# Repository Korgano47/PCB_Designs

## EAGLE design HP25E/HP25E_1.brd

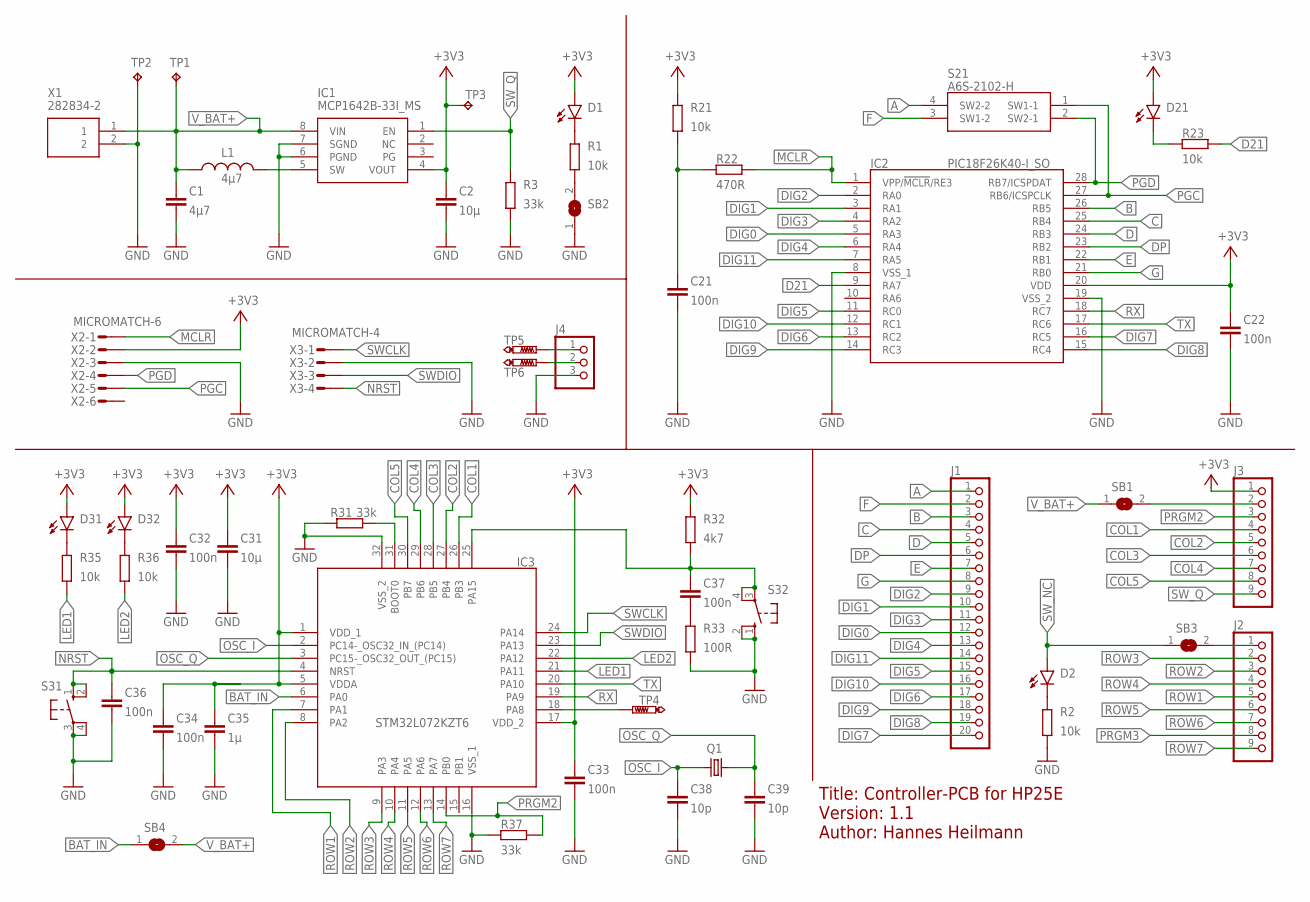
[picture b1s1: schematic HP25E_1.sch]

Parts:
C1: 4µ7; C1206K
C2, C31: 10µ; C1206K
C21, C22, C32, C33, C34, C36, C37: 100n; C0805K
C35: 1µ; C1206K
C38, C39: 10p; C0805K
D1, D2, D21, D31, D32: LEDSML0805; SML0805
IC1: MCP1642B-33I_MS; SOP65P490X110-8N
IC2: PIC18F26K40-I_SO; SOIC127P1030X265-28N
IC3: STM32L072KZT6; QFP80P900X900X160-32N
J1: PINHD-1X20-BIG; 1X20-BIG
J2, J3: PINHD-1X9; 1X09-BIG
J4: PINHD-1X3; 1X03
L1: 4µ7; L4532P
Q1: CRYSTALMM20SS; MM20SS
R1, R2, R21, R23, R35, R36: 10k; R0805
R3, R31, R37: 33k; R0805
R22: 470R; R0805
R32: 4k7; R0805
R33: 100R; R0805
S21: A6S-2102-H; SOP254P980X450-4N
S31, S32: 10-XX; B3F-10XX
SB1, SB2, SB3, SB4: SJ
TP1, TP2, TP3: TPB1,27; B1,27
TP4: PTR1B1,27; B1,27
TP5, TP6: PTR1PAD1-13; P1-13
X1: 282834-2; SHDR2W85P0X254_1X2_554X650X103
X2: MICROMATCH-6
X3: MICROMATCH-4

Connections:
+3V3: C2.1, C22.1, C31.1, C32.1, C33.1, C34.1, C35.1, D1.A, D21.A, D31.A, D32.A, IC1.4 (VOUT), IC2.20 (VDD), IC3.1 (VDD_1), IC3.5 (VDDA), IC3.17 (VDD_2), J3.1, R21.2, R32.2, TP3.TP, X2.2
A: J1.1, S21.4 (SW2-2)
B: IC2.26 (RB5), J1.3
BAT_IN: IC3.6 (PA0), SB4.1
C: IC2.25 (RB4), J1.4
COL1: IC3.26 (PB3), J3.4
COL2: IC3.27 (PB4), J3.5
COL3: IC3.28 (PB5), J3.6
COL4: IC3.29 (PB6), J3.7
COL5: IC3.30 (PB7), J3.8
D: IC2.24 (RB3), J1.5
D21: IC2.9 (RA7), R23.1
DIG0: IC2.5 (RA3), J1.12
DIG1: IC2.3 (RA1), J1.10
DIG2: IC2.2 (RA0), J1.9
DIG3: IC2.4 (RA2), J1.11
DIG4: IC2.6 (RA4), J1.13
DIG5: IC2.11 (RC0), J1.15
DIG6: IC2.13 (RC2), J1.17
DIG7: IC2.16 (RC5), J1.20
DIG8: IC2.15 (RC4), J1.19
DIG9: IC2.14 (RC3), J1.18
DIG10: IC2.12 (RC1), J1.16
DIG11: IC2.7 (RA5), J1.14
DP: IC2.23 (RB2), J1.6
E: IC2.22 (RB1), J1.7
F: J1.2, S21.3 (SW1-2)
G: IC2.21 (RB0), J1.8
GND: C1.2, C2.2, C21.2, C22.2, C31.2, C32.2, C33.2, C34.2, C35.2, C36.2, C38.2, C39.2, IC1.6 (PGND), IC1.7 (SGND), IC2.8 (VSS_1), IC2.19 (VSS_2), IC3.16 (VSS_1), IC3.32 (VSS_2), J4.3, R2.1, R3.1, R31.2, R33.1, R37.2, S31.3, S31.4 (P1), S32.1 (S), S32.2 (S1), SB2.1, TP2.TP, X1.2, X2.3, X3.2
LED1: IC3.21 (PA11), R35.1
LED2: IC3.22 (PA12), R36.1
MCLR: IC2.1 (VPP/!MCLR!/RE3), R22.2, X2.1
unnamed: IC1.5 (SW), L1.1
unnamed: D21.C, R23.2
unnamed: C21.1, R21.1, R22.1
unnamed: D1.C, R1.2
unnamed: D2.C, R2.2
unnamed: C37.1, IC3.25 (PA15), R32.1, S32.3, S32.4 (P1)
unnamed: C37.2, R33.2
unnamed: J2.1, SB3.2
unnamed: IC3.31 (BOOT0), R31.1
unnamed: R1.1, SB2.2
unnamed: D32.C, R36.2
unnamed: D31.C, R35.2
unnamed: J4.2, TP6.TP
unnamed: J4.1, TP5.TP
unnamed: IC3.18 (PA8), TP4.TP
NRST: C36.1, IC3.4 (NRST), S31.1 (S), S31.2 (S1), X3.4
OSC_I: C38.1, IC3.2 (PC14-_OSC32_IN_(PC14)), Q1.1
OSC_Q: C39.1, IC3.3 (PC15-_OSC32_OUT_(PC15)), Q1.4 (2)
PGC: IC2.27 (RB6/ICSPCLK), S21.1 (SW1-1), X2.5
PGD: IC2.28 (RB7/ICSPDAT), S21.2 (SW2-1), X2.4
PRGM2: IC3.14 (PB0), J3.3, R37.1
PRGM3: J2.8
ROW1: IC3.7 (PA1), J2.5
ROW2: IC3.8 (PA2), J2.3
ROW3: IC3.9 (PA3), J2.2
ROW4: IC3.10 (PA4), J2.4
ROW5: IC3.11 (PA5), J2.6
ROW6: IC3.12 (PA6), J2.7
ROW7: IC3.13 (PA7), J2.9
RX: IC2.18 (RC7), IC3.19 (PA9)
SWCLK: IC3.24 (PA14), X3.1
SWDIO: IC3.23 (PA13), X3.3
SW_I: J3.2, SB1.2
SW_NC: D2.A, SB3.1
SW_Q: IC1.1 (EN), J3.9, R3.2
TX: IC2.17 (RC6), IC3.20 (PA10)
V_BAT+: C1.1, IC1.8 (VIN), L1.2, SB1.1, SB4.2, TP1.TP, X1.1

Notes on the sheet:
Title: Controller-PCB for HP25E Version: 1.1 Author: Hannes Heilmann

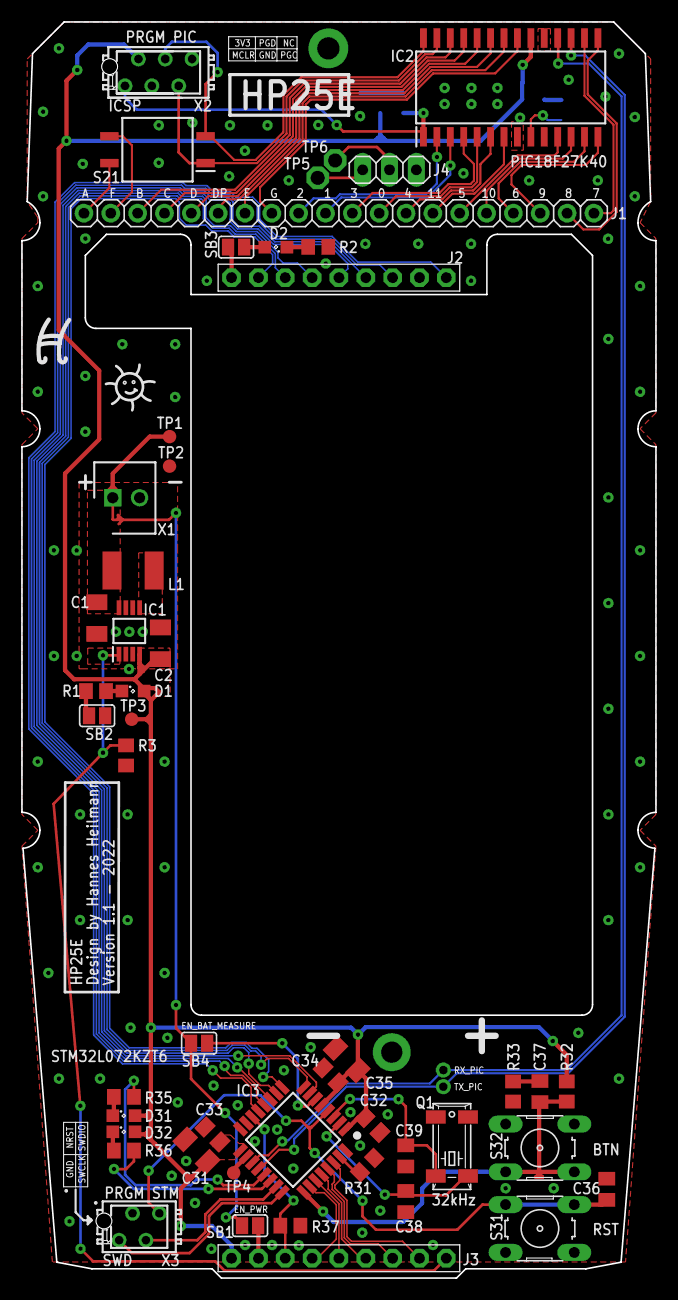
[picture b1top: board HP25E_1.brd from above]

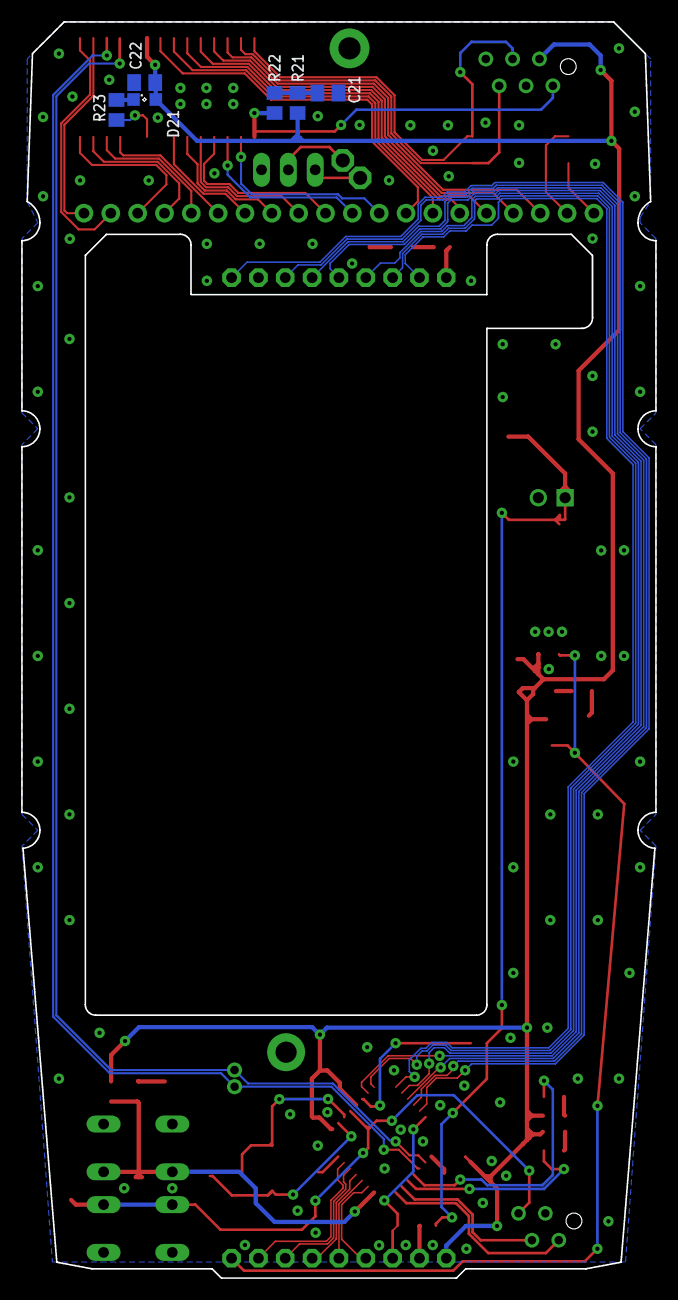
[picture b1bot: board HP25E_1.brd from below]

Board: 2 copper layers, 60.0 x 118.9 mm, 55 parts (6 on the bottom side), 68 nets.

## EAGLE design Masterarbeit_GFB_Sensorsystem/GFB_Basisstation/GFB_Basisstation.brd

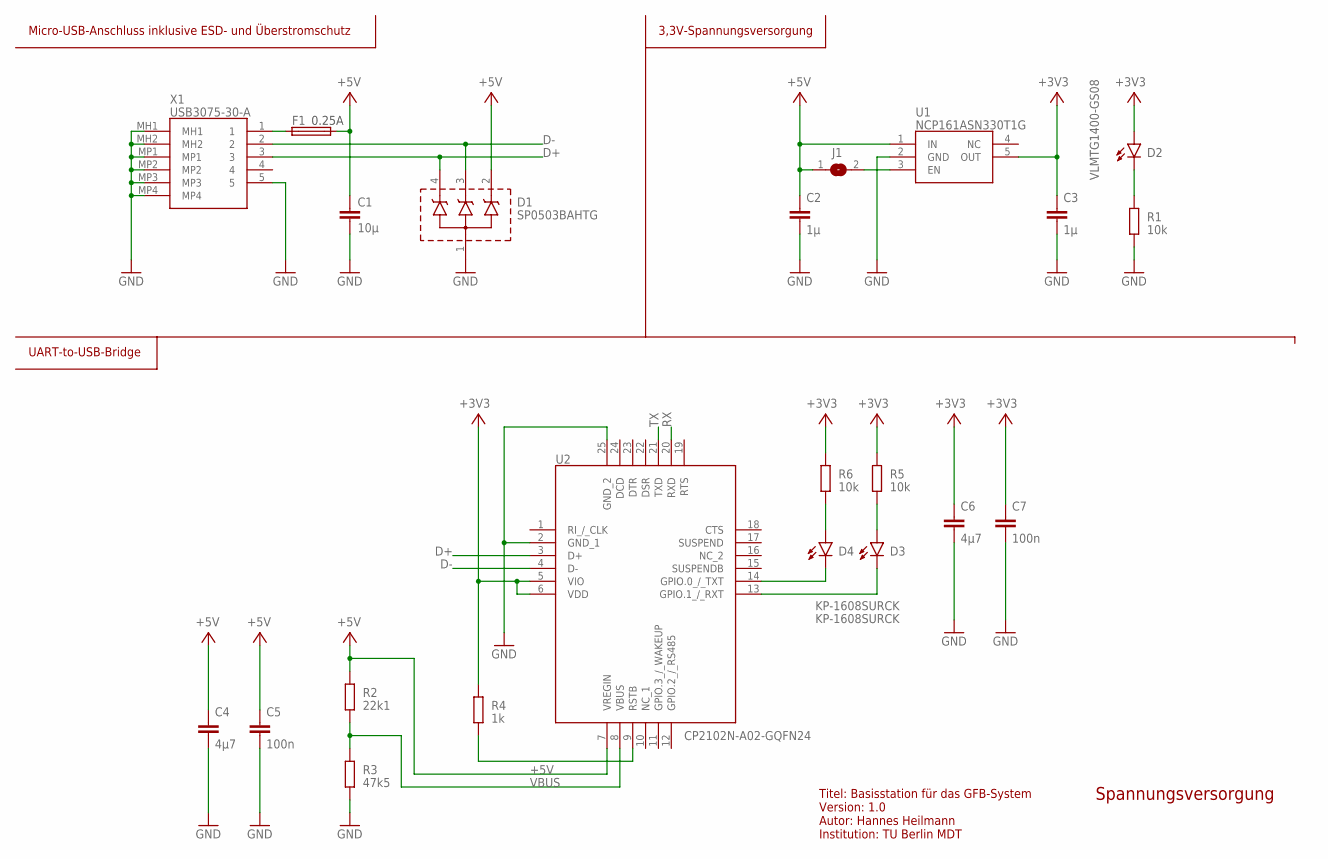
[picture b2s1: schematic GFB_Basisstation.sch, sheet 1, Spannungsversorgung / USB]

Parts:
C1: 10µ; PATCHPOLYGRAPHV1_1608M
C2, C3: 1µ; PATCHPOLYGRAPHV1_1608M
C4, C6: 4µ7; PATCHPOLYGRAPHV1_1608M
C5, C7: 100n; PATCHPOLYGRAPHV1_1608M
D1: SP0503BAHTG
D2: VLMTG1400-GS08; CHIPLED_0603
D3, D4: KP-1608SURCK; CHIPLED_0603
F1: SF-0603FP025F-2; R0603
J1: SJ
R1, R5, R6: 10k; PATCHPOLYGRAPHV1_1608M
R2: 22k1; PATCHPOLYGRAPHV1_1608M
R3: 47k5; PATCHPOLYGRAPHV1_1608M
R4: 1k; PATCHPOLYGRAPHV1_1608M
U1: NCP161ASN330T1G; SOT95P280X145-5N
U2: CP2102N-A02-GQFN24; QFN50P400X400X80-25N
X1: USB3075-30-A; USB307530A

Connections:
+3V3: C3.1, C6.1, C7.1, D2.A, R4.1, R5.1, R6.1, U1.5 (OUT), U2.5 (VIO), U2.6 (VDD); also elsewhere on the board
+5V: C1.1, C2.1, C4.1, C5.1, D1.2 (K_1), F1.2, J1.1, R2.1, U1.1 (IN), U2.7 (VREGIN)
D+: D1.4 (K_3), U2.3 (D+), X1.3
D-: D1.3 (K_2), U2.4 (D-), X1.2
GND: C1.2, C2.2, C3.2, C4.2, C5.2, C6.2, C7.2, D1.1 (COMMON_A), R1.2, R3.2, U1.2 (GND), U2.2 (GND_1), U2.25 (GND_2), X1.5, X1.MH1, X1.MH2, X1.MP1, X1.MP2, X1.MP3, X1.MP4; also elsewhere on the board
unnamed: D2.C, R1.1
unnamed: D3.A, R5.2
unnamed: R4.2, U2.9 (RSTB)
unnamed: D4.A, R6.2
unnamed: F1.1, X1.1
unnamed: D3.C, U2.13 (GPIO.1_/_RXT)
unnamed: D4.C, U2.14 (GPIO.0_/_TXT)
unnamed: J1.2, U1.3 (EN)
RX: U2.20 (RXD); also elsewhere on the board
TX: U2.21 (TXD); also elsewhere on the board
VBUS: R2.2, R3.1, U2.8 (VBUS)

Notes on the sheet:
0.25A
Spannungsversorgung
Titel: Basisstation für das GFB-System Version: 1.0 Autor: Hannes Heilmann Institution: TU Berlin MDT
Micro-USB-Anschluss inklusive ESD- und Überstromschutz
3,3V-Spannungsversorgung
UART-to-USB-Bridge

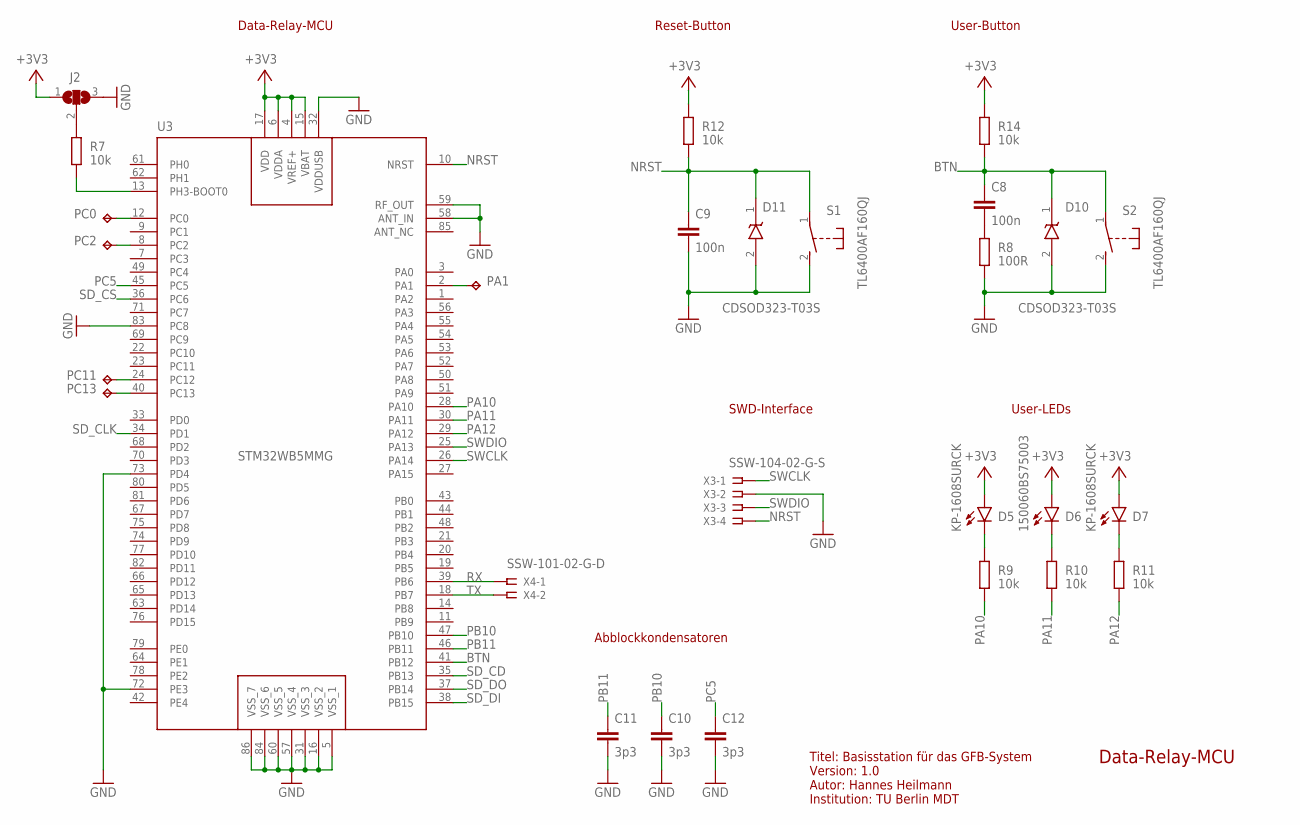
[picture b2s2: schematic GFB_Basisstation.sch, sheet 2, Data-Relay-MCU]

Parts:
C8, C9: 100n; PATCHPOLYGRAPHV1_1608M
C10, C11, C12: 3p3; PATCHPOLYGRAPHV1_1608M
D5, D7: KP-1608SURCK; CHIPLED_0603
D6: 150060BS75003; CHIPLED_0603
D10, D11: CDSOD323-T03S; SOD2513X114N
J2: JUMPER_3JUMPER_3_0603; JUMPER_3_0603
PA1: TPTP06R; TP06R
PC0, PC2, PC11, PC13: TPTP06R; TP06R
R7, R9, R10, R11, R12, R14: 10k; PATCHPOLYGRAPHV1_1608M
R8: 100R; PATCHPOLYGRAPHV1_1608M
S1, S2: TL6400AF160QJ
U3: STM32WB5MMG
X3: SSW-104-02-G-S
X4: SSW-101-02-G-D

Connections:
+3V3: D5.A, D6.A, D7.A, J2.1, R12.1, R14.1, U3.4 (VREF+), U3.6 (VDDA), U3.15 (VBAT), U3.17 (VDD); also elsewhere on the board
BTN: C8.1, D10.1 (K), R14.2, S2.1, U3.41 (PB12)
GND: C9.2, C10.2, C11.2, C12.2, D10.2 (A), D11.2 (A), J2.3, R8.2, S1.2 (S), S2.2 (S), U3.5 (VSS_1), U3.16 (VSS_2), U3.31 (VSS_3), U3.32 (VDDUSB), U3.57 (VSS_4), U3.58 (ANT_IN), U3.59 (RF_OUT), U3.60 (VSS_5), U3.72 (PE3), U3.73 (PD4), U3.83 (PC8), U3.84 (VSS_6), U3.86 (VSS_7), X3.2; also elsewhere on the board
unnamed: PC2.TP, U3.8 (PC2)
unnamed: R7.2, U3.13 (PH3-BOOT0)
unnamed: PC11.TP, U3.24 (PC12)
unnamed: C8.2, R8.1
unnamed: D6.C, R10.1
unnamed: D7.C, R11.1
unnamed: D5.C, R9.1
unnamed: PC13.TP, U3.40 (PC13)
unnamed: J2.2, R7.1
unnamed: PA1.TP, U3.2 (PA1)
NRST: C9.1, D11.1 (K), R12.2, S1.1, U3.10 (NRST), X3.4
PA10: R9.2, U3.28 (PA10)
PA11: R10.2, U3.30 (PA11)
PA12: R11.2, U3.29 (PA12)
PB10: C10.1, U3.47 (PB10)
PB11: C11.1, U3.46 (PB11)
PC0: PC0.TP, U3.12 (PC0)
PC5: C12.1, U3.45 (PC5)
RX: U3.39 (PB6), X4.1; also elsewhere on the board
SD_CD: U3.35 (PB13); also elsewhere on the board
SD_CLK: U3.34 (PD1); also elsewhere on the board
SD_CS: U3.36 (PC6); also elsewhere on the board
SD_DI: U3.38 (PB15); also elsewhere on the board
SD_DO: U3.37 (PB14); also elsewhere on the board
SWCLK: U3.26 (PA14), X3.1
SWDIO: U3.25 (PA13), X3.3
TX: U3.18 (PB7), X4.2; also elsewhere on the board

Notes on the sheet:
STM32WB5MMG
Titel: Basisstation für das GFB-System Version: 1.0 Autor: Hannes Heilmann Institution: TU Berlin MDT
Data-Relay-MCU
Reset-Button
User-Button
SWD-Interface
User-LEDs
Abblockkondensatoren

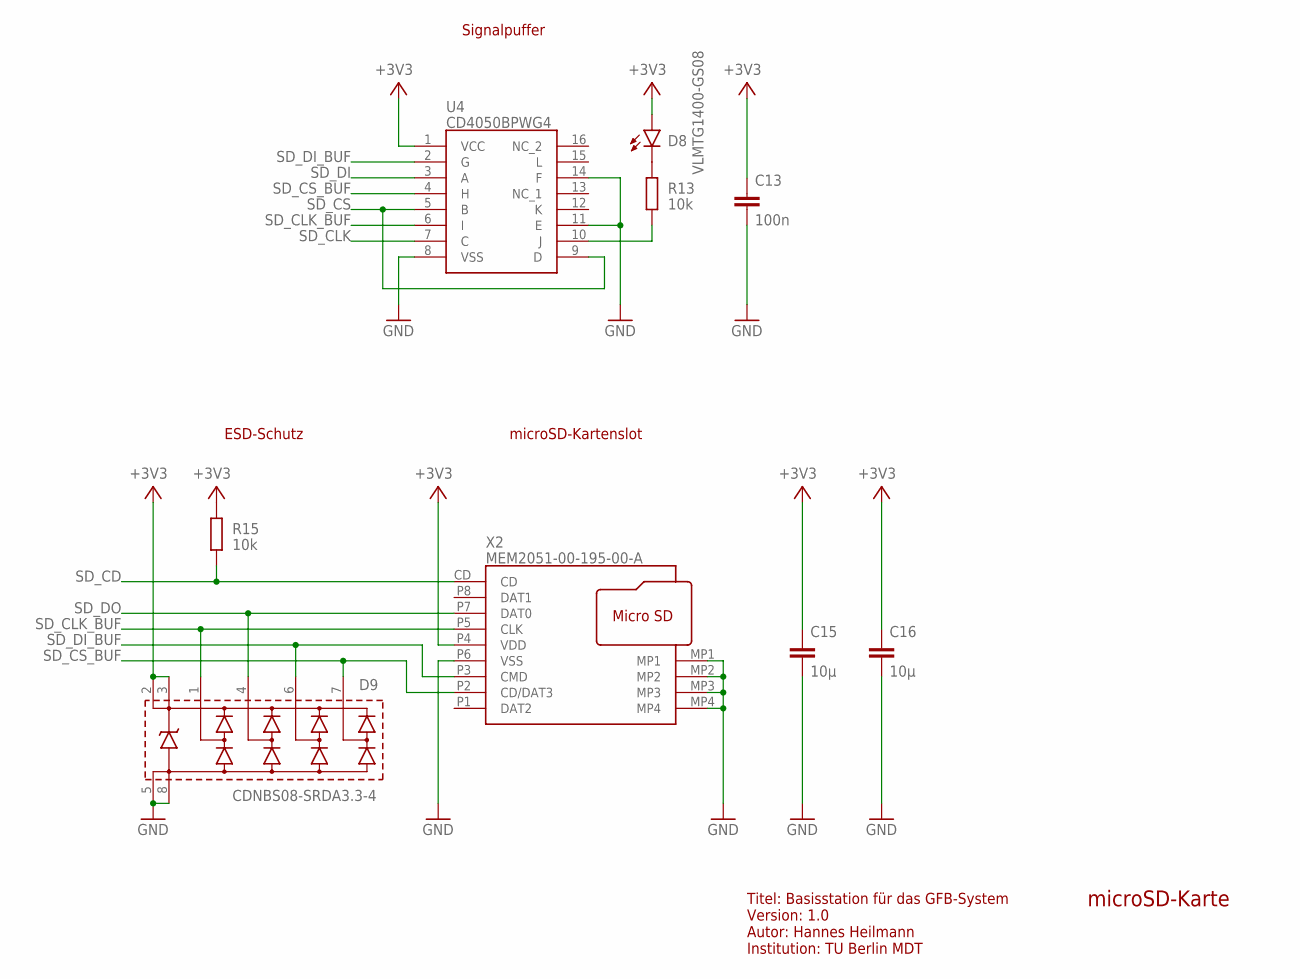
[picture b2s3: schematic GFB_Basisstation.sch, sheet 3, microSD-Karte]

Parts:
C13: 100n; PATCHPOLYGRAPHV1_1608M
C15, C16: 10μ; PATCHPOLYGRAPHV1_1608M
D8: VLMTG1400-GS08; CHIPLED_0603
D9: CDNBS08-SRDA3.3-4; SOIC127P600X175-8N
R13, R15: 10k; PATCHPOLYGRAPHV1_1608M
U4: CD4050BPWG4; SOP65P640X120-16N
X2: MEM2051-00-195-00-A; MEM20510019500A

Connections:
+3V3: C13.1, C15.1, C16.1, D8.A, D9.2 (+VREF_1), D9.3 (+VREF_2), R15.1, U4.1 (VCC), X2.P4 (VDD); also elsewhere on the board
GND: C13.2, C15.2, C16.2, D9.5 (GND_1), D9.8 (GND_2), U4.8 (VSS), U4.11 (E), U4.14 (F), X2.MP1, X2.MP2, X2.MP3, X2.MP4, X2.P6 (VSS); also elsewhere on the board
unnamed: R13.2, U4.10 (J)
unnamed: D8.C, R13.1
SD_CD: R15.2, X2.CD; also elsewhere on the board
SD_CLK: U4.7 (C); also elsewhere on the board
SD_CLK_BUF: D9.1 (I/O_1), U4.6 (I), X2.P5 (CLK)
SD_CS: U4.5 (B), U4.9 (D); also elsewhere on the board
SD_CS_BUF: D9.7 (I/O_4), U4.4 (H), X2.P2 (CD/DAT3)
SD_DI: U4.3 (A); also elsewhere on the board
SD_DI_BUF: D9.6 (I/O_3), U4.2 (G), X2.P3 (CMD)
SD_DO: D9.4 (I/O_2), X2.P7 (DAT0); also elsewhere on the board

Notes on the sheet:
Titel: Basisstation für das GFB-System Version: 1.0 Autor: Hannes Heilmann Institution: TU Berlin MDT
microSD-Karte
microSD-Kartenslot
ESD-Schutz
Signalpuffer

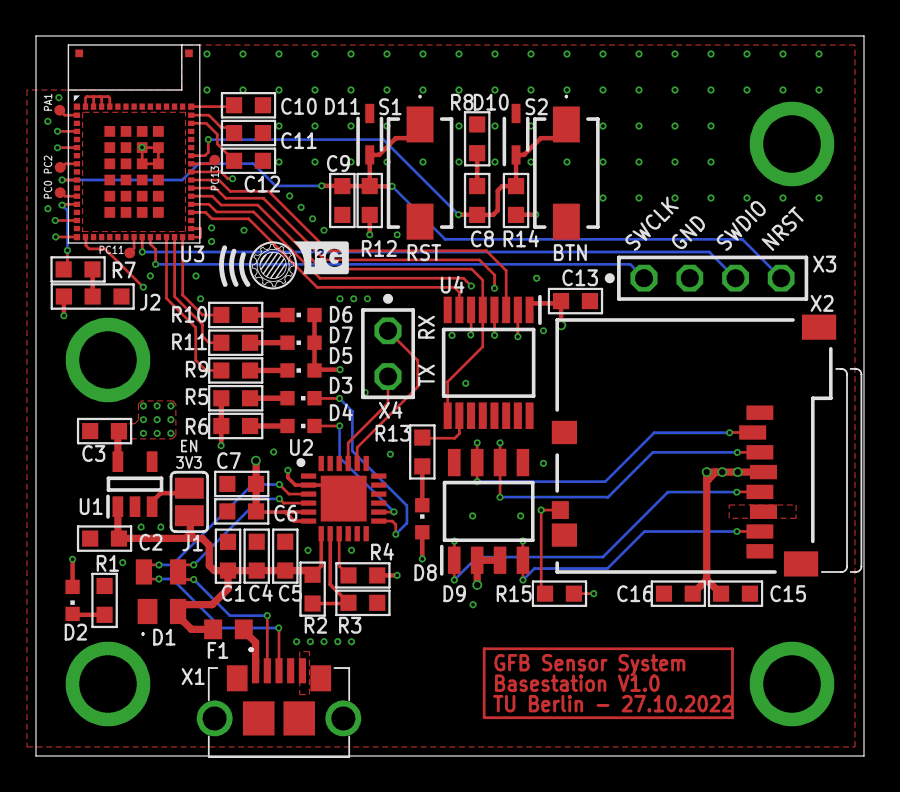
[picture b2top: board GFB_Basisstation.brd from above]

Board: 4 copper layers, 46.0 x 40.0 mm, 59 parts (0 on the bottom side), 47 nets.
